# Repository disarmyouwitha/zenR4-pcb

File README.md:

# Steno Squid QSPI expansion module

Current hardware work is the [Steno Squid eight-contact daughterboard](projects/steno-squid/README.md) for the Boardsource Wireless Corne SMT. Its first electrical proposal is available in native KiCad. Connector dimensions, supply verification and exact flash package are the next design inputs.

## Completed Draft-Corne routing reference

# Draft-Corne: Choc Corne with left flash / right nice!view

**[Draft C files and status](projects/choc-corne-flash/draft-c/README.md)** · [ChatGPT handoff](docs/CHATGPT-HANDOFF.md) · [Download packet](docs/draft-corne.zip)

Both nice!nanos mount on the front, components down. Our tested matrix and left QSPI are retained; the right has a real nice!view interface. Battery connections use back-side solder pads. Both halves are routed and pass KiCad ERC, DRC, and schematic parity checks. Physical assembly still needs verification.

Repository remains private; preserve [source attribution](ATTRIBUTION.md). The older Draft B information below is historical.

---

# zenR4-pcb — Nano Independent

Historical Draft B direction: our own 42-key Choc nice!nano keyboard and case, inspired by Zen geometry. The owner is pursuing an original spare PCB for their Zen; integrated replacement development is set aside.

## Historical draft: B

- Old rear USB reliefs removed; USB-C comes from the nice!nano.
- Thumb clearance bubble replaced by a smooth, mirrored contour.
- All electrical objects and switch centers preserved from Draft A.
- Both halves pass native ERC, DRC, unconnected and schematic parity checks with zero issues.

**[Open Draft B](projects/nano-independent/draft-b/README.md)** · [Thumb before/after](projects/nano-independent/draft-b/thumb-before-after.png) · [Current ChatGPT handoff](docs/CHATGPT-HANDOFF.md) · [Download Draft B packet](docs/nano-independent-draft-b.zip)

Right nice!view, optional flash population, optional RGB and squid art remain the target. Their new display/RGB circuits and the new case are not implemented by this outline-only revision. See [project direction](projects/nano-independent/README.md).

Open the `zen-r4-left.kicad_pro` / `zen-r4-right.kicad_pro` under `projects/nano-independent/draft-b/`. `r4-layout/` is the unchanged Draft A baseline, also tagged `draft-a-baseline`; its old case-fit notes and upload ZIP are historical. Experimental generators can overwrite finished work.

For tomorrow's ChatGPT discussion, use [START-HERE](docs/START-HERE.md). Private GitHub links may require your signed-in account; upload the handoff/images if ChatGPT cannot read the repo.

Repository visibility remains private. Restricted source CAD and derived files retain their attribution and source restrictions; see [ATTRIBUTION](ATTRIBUTION.md). No hardware/fabrication order or production readiness is claimed.

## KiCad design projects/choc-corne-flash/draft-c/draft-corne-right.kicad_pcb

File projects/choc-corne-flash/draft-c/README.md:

# Draft-Corne (Draft C)

42-key Typeractive-style Choc-spaced Corne with our tested matrix, left QSPI flash and right nice!view. This is a routed development draft, not a manufacturing release. The geometry was reconstructed from a public 3D model; it is not Typeractive's original PCB source. See the reference folder and root ATTRIBUTION.md.

Open `draft-corne-left.kicad_pro` or `draft-corne-right.kicad_pro` beside their matching schematic and PCB. Keep the local symbol library, footprint directory and library tables with the files.

## Assembly direction

- Both nice!nanos mount on the **front**, with **components facing down** toward the carrier PCB, as explicitly requested. Both have the same physical pin-bank orientation: top view, USB up, carrier U1 pad 1 is on the right and pad 13 on the left.
- Choc sockets and diodes are on the back. The left top-row innermost socket SW6 is rotated 180 degrees and D6 moved to avoid mounting-hole/socket clearances; its switch center and electrical assignment are unchanged.
- Left flash U2 and local 100 nF C1 / 10 kΩ R1 occupy the former JST electronics region, on the front. Candidate flash is W25Q128JVSIQ, **208-mil SOIC**, not the narrower SOIC package.
- Battery J1 is a pair of **back-side solder pads**: 1 BAT+, 2 GND. No JST. Plan strain relief and insulated battery retention in the new enclosure. Reset is on the opposite face in this area.
- Right J2 supplies a nice!view above the nano. Routing moved J2 1.8 mm toward the thumbs to clear the carrier’s antenna keepout. Check display height and solder access with the actual parts.
- Power/reset footprints are candidates (MSK12C02 / TL3342), pending exact purchased-part drawing checks. The battery switch disconnects the cell; USB can still power the nano. Charging while switched off is not promised.

## Pin plan

Both halves retain ROW0–3 = D8, D9, D21, D20; COL0–5 outside→seam = D19, D18, D15, D14, D0, D1. Col2row diodes; right firmware reverses column scan with global offset 6. This is **our matrix**, not stock Typeractive D4–D7 rows.

Left flash CS#/CLK/IO0/IO1/IO2/IO3 = D2/D4/D5/D6/D7/D3, plus switched 3V3 and GND. The nano controls the switched rail internally using P0.13; that GPIO is not a carrier edge pad.

Right nice!view J2, viewed from the front, left→right:

| Pad | Signal | nice!nano |
|---|---|---|
| 1 | MOSI | D2 / P0.17 |
| 2 | SCK | D3 / P0.20 |
| 3 | VCC | switched 3V3 |
| 4 | GND | GND |
| 5 | CS, active high | D4 / P0.22 |

The custom right CS is D4; the existing Ultralight's D0 CS cannot be copied because D0 is one of our matrix columns. Working hardware/firmware has not been altered.

## Checks and remaining work

Both halves have **zero unrouted connections, DRC violations, schematic parity issues, and ERC violations** in KiCad 10.0.7. Both copper layers have filled ground planes. The carrier’s antenna keepout remains clear. See `validation.json` for hashes and configured checks. The DSN/SES files and placement/router reports are records of the initial routing pass.

Physical assembly remains unverified. Check the nano and display stack, the selected footprints against the parts, and battery retention before fabrication.

Official display references are the [pinout](https://nicekeyboards.com/docs/nice-view/pinout-schematic/) and [dimensions](https://nicekeyboards.com/static/2f2592ff1ff8021932814b20cb76e3c4/a6d36/niceview_dimensions.png).

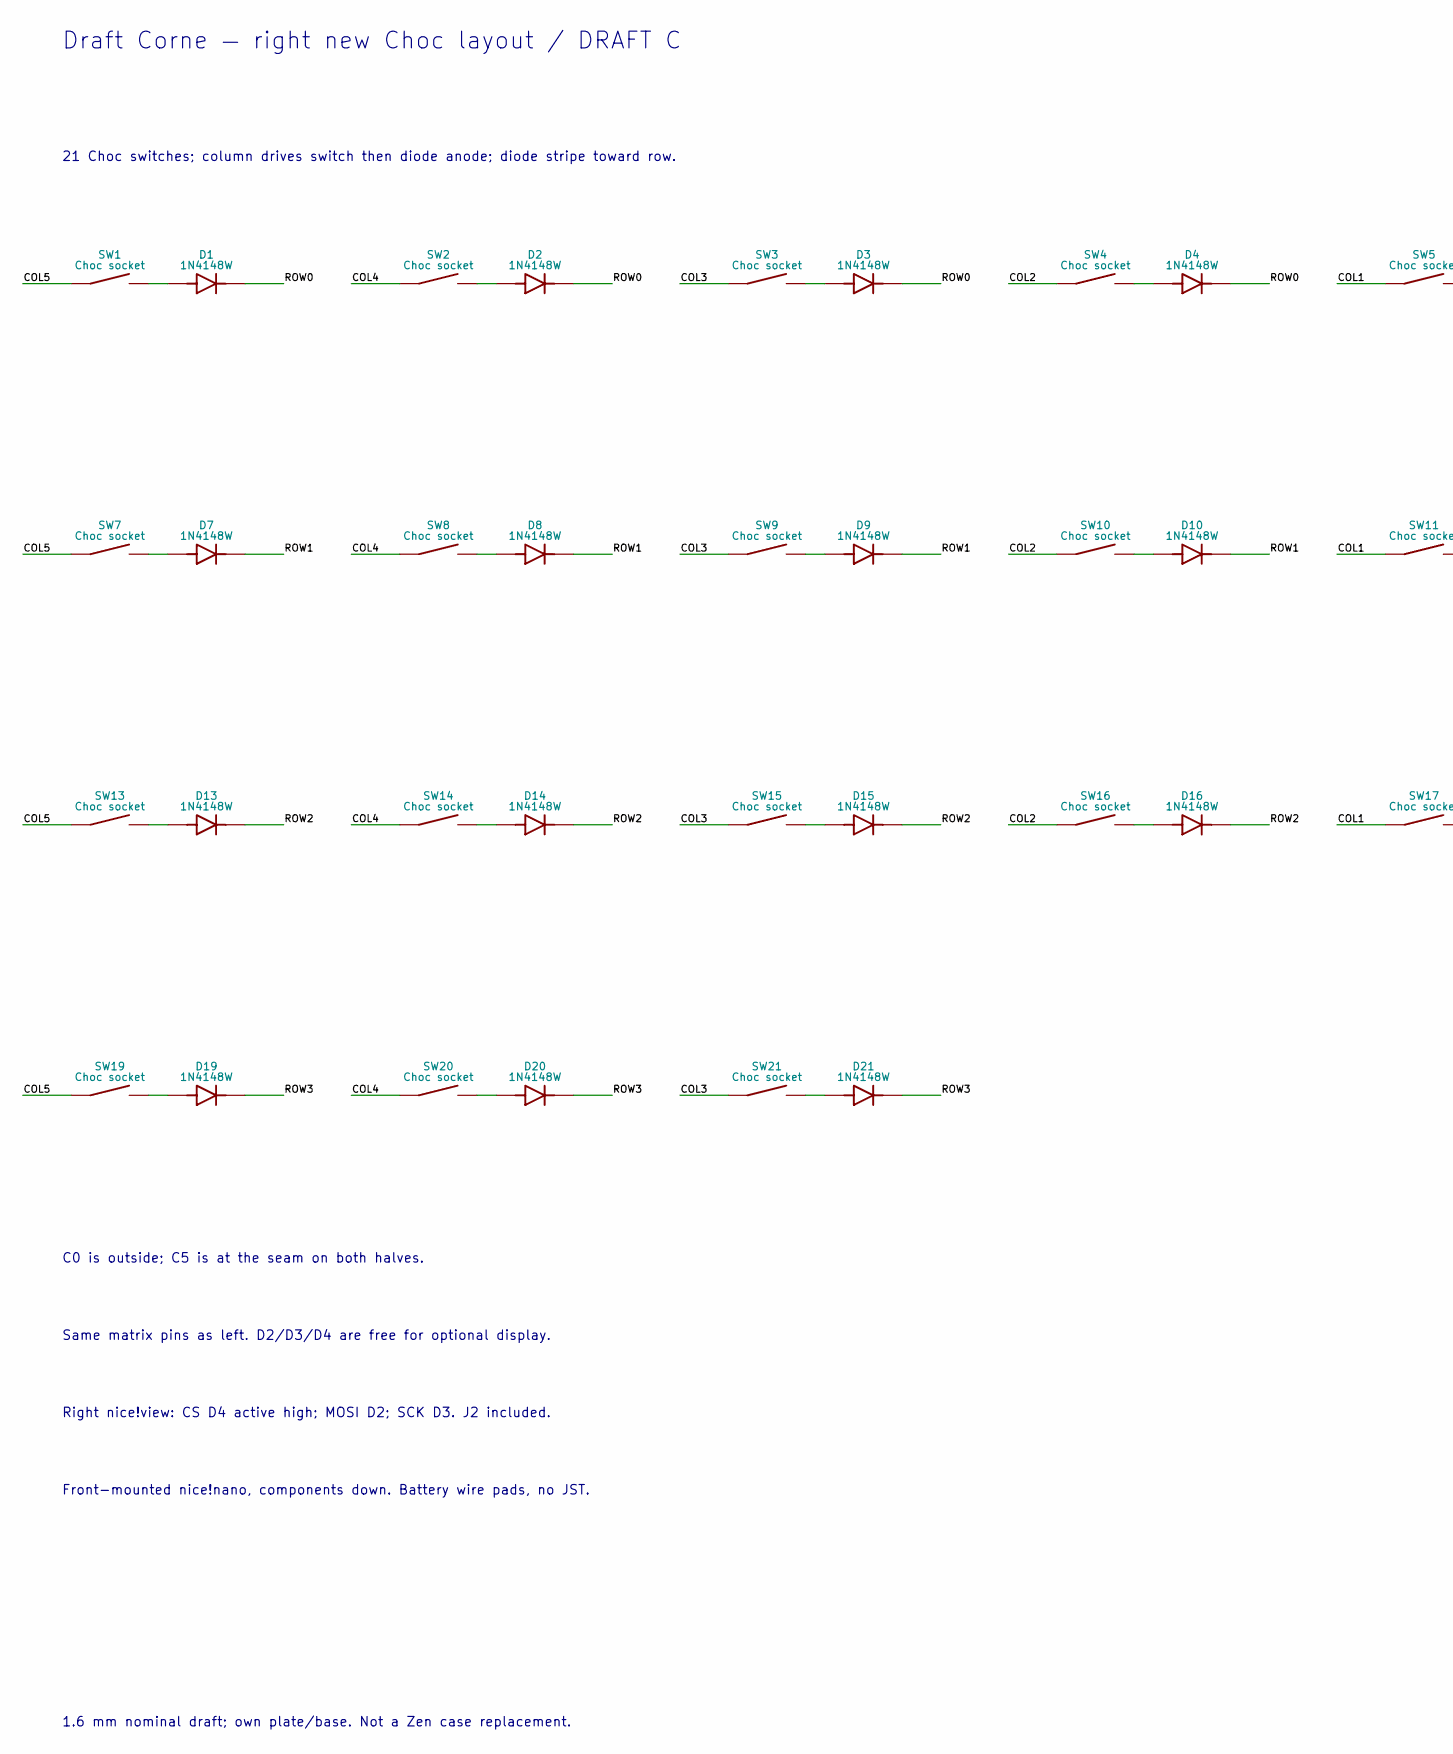
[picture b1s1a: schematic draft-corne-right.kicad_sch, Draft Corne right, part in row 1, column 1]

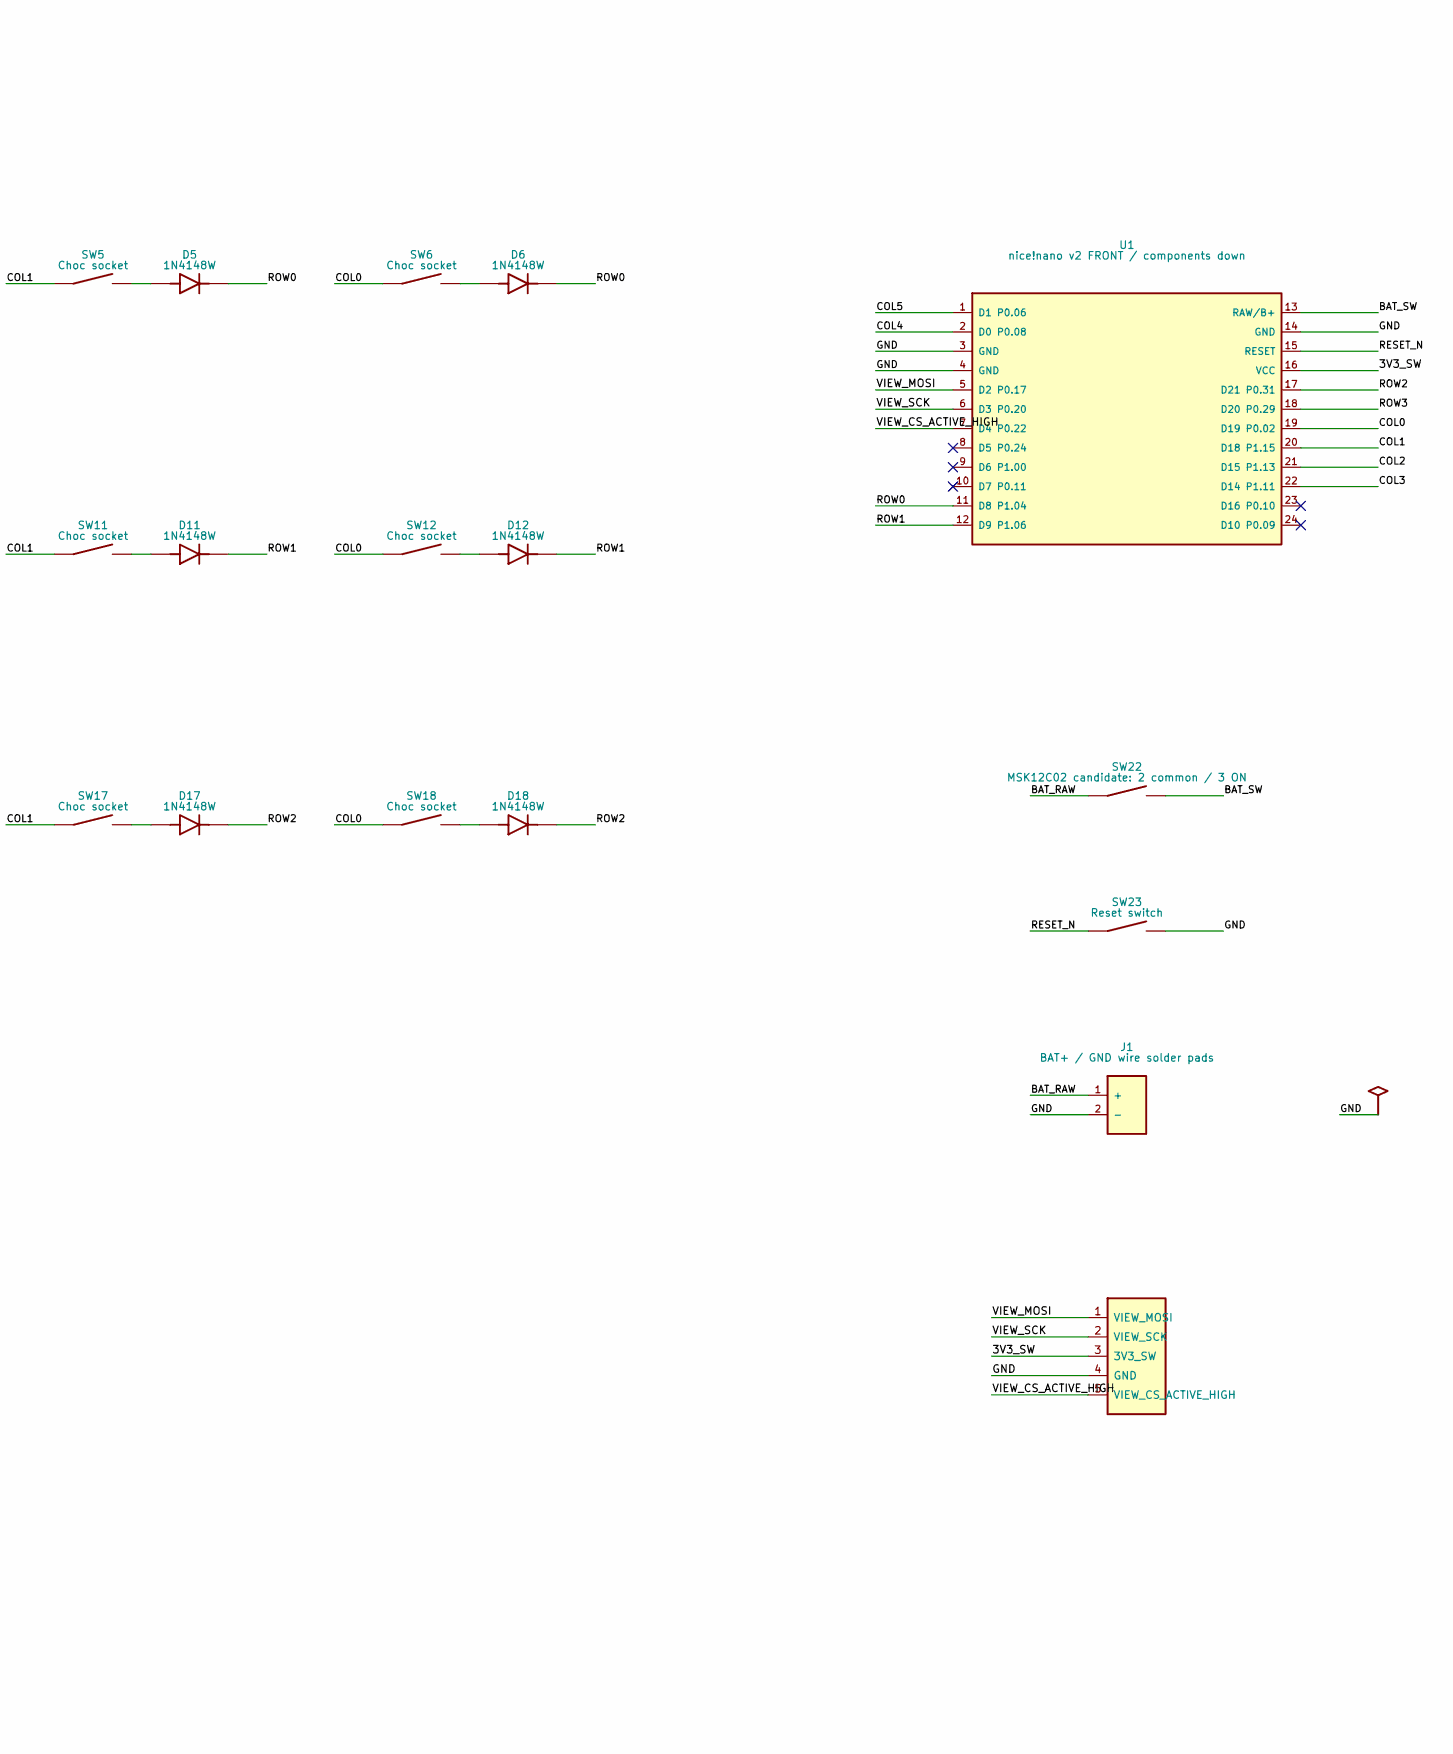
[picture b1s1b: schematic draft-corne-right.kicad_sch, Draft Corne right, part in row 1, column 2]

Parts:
D1, D2, D3, D4, D5, D6, D7, D8, D9, D10, D11, D12, D13, D14, D15, D16, D17, D18, D19, D20, D21: 1N4148W; Diode_SOD123_Bottom
J1: BAT+ / GND wire solder pads; Battery_Wire_SMD
J2: nice!view front header; NiceView_Front_Header
SW1, SW2, SW3, SW4, SW5, SW6, SW7, SW8, SW9, SW10, SW11, SW12, SW13, SW14, SW15, SW16, SW17, SW18, SW19, SW20, SW21: Choc socket; ChocSocket_Bottom
SW22: MSK12C02 candidate: 2 common / 3 ON; Power_MSK12C02
SW23: Reset switch; Reset_TL3342
U1: nice!nano v2 FRONT / components down; Nano_Front_Down

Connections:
/3V3_SW: J2.3 (3V3_SW), U1.16 (VCC)
/BAT_RAW: J1.1 (+), SW22.2 (1)
/BAT_SW: SW22.3 (2), U1.13 (RAW/B+)
/COL0: SW6.1, SW12.1, SW18.1, U1.19 (D19 P0.02)
/COL1: SW5.1, SW11.1, SW17.1, U1.20 (D18 P1.15)
/COL2: SW4.1, SW10.1, SW16.1, U1.21 (D15 P1.13)
/COL3: SW3.1, SW9.1, SW15.1, SW21.1, U1.22 (D14 P1.11)
/COL4: SW2.1, SW8.1, SW14.1, SW20.1, U1.2 (D0 P0.08)
/COL5: SW1.1, SW7.1, SW13.1, SW19.1, U1.1 (D1 P0.06)
/GND: J1.2 (-), J2.4 (GND), SW23.2, U1.3 (GND), U1.4 (GND), U1.14 (GND)
/RESET_N: SW23.1, U1.15 (RESET)
/ROW0: D1.1 (K), D2.1 (K), D3.1 (K), D4.1 (K), D5.1 (K), D6.1 (K), U1.11 (D8 P1.04)
/ROW1: D7.1 (K), D8.1 (K), D9.1 (K), D10.1 (K), D11.1 (K), D12.1 (K), U1.12 (D9 P1.06)
/ROW2: D13.1 (K), D14.1 (K), D15.1 (K), D16.1 (K), D17.1 (K), D18.1 (K), U1.17 (D21 P0.31)
/ROW3: D19.1 (K), D20.1 (K), D21.1 (K), U1.18 (D20 P0.29)
/VIEW_CS_ACTIVE_HIGH: J2.5 (VIEW_CS_ACTIVE_HIGH), U1.7 (D4 P0.22)
/VIEW_MOSI: J2.1 (VIEW_MOSI), U1.5 (D2 P0.17)
/VIEW_SCK: J2.2 (VIEW_SCK), U1.6 (D3 P0.20)
unnamed: D1.2 (A), SW1.2
unnamed: D2.2 (A), SW2.2
unnamed: D3.2 (A), SW3.2
unnamed: D4.2 (A), SW4.2
unnamed: D5.2 (A), SW5.2
unnamed: D6.2 (A), SW6.2
unnamed: D7.2 (A), SW7.2
unnamed: D8.2 (A), SW8.2
unnamed: D9.2 (A), SW9.2
unnamed: D10.2 (A), SW10.2
unnamed: D11.2 (A), SW11.2
unnamed: D12.2 (A), SW12.2
unnamed: D13.2 (A), SW13.2
unnamed: D14.2 (A), SW14.2
unnamed: D15.2 (A), SW15.2
unnamed: D16.2 (A), SW16.2
unnamed: D17.2 (A), SW17.2
unnamed: D18.2 (A), SW18.2
unnamed: D19.2 (A), SW19.2
unnamed: D20.2 (A), SW20.2
unnamed: D21.2 (A), SW21.2

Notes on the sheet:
Draft Corne — right new Choc layout / DRAFT C
21 Choc switches; column drives switch then diode anode; diode stripe toward row.
C0 is outside; C5 is at the seam on both halves.
Same matrix pins as left. D2/D3/D4 are free for optional display.
Right nice!view: CS D4 active high; MOSI D2; SCK D3. J2 included.
Front-mounted nice!nano, components down. Battery wire pads, no JST.
1.6 mm nominal draft; own plate/base. Not a Zen case replacement.

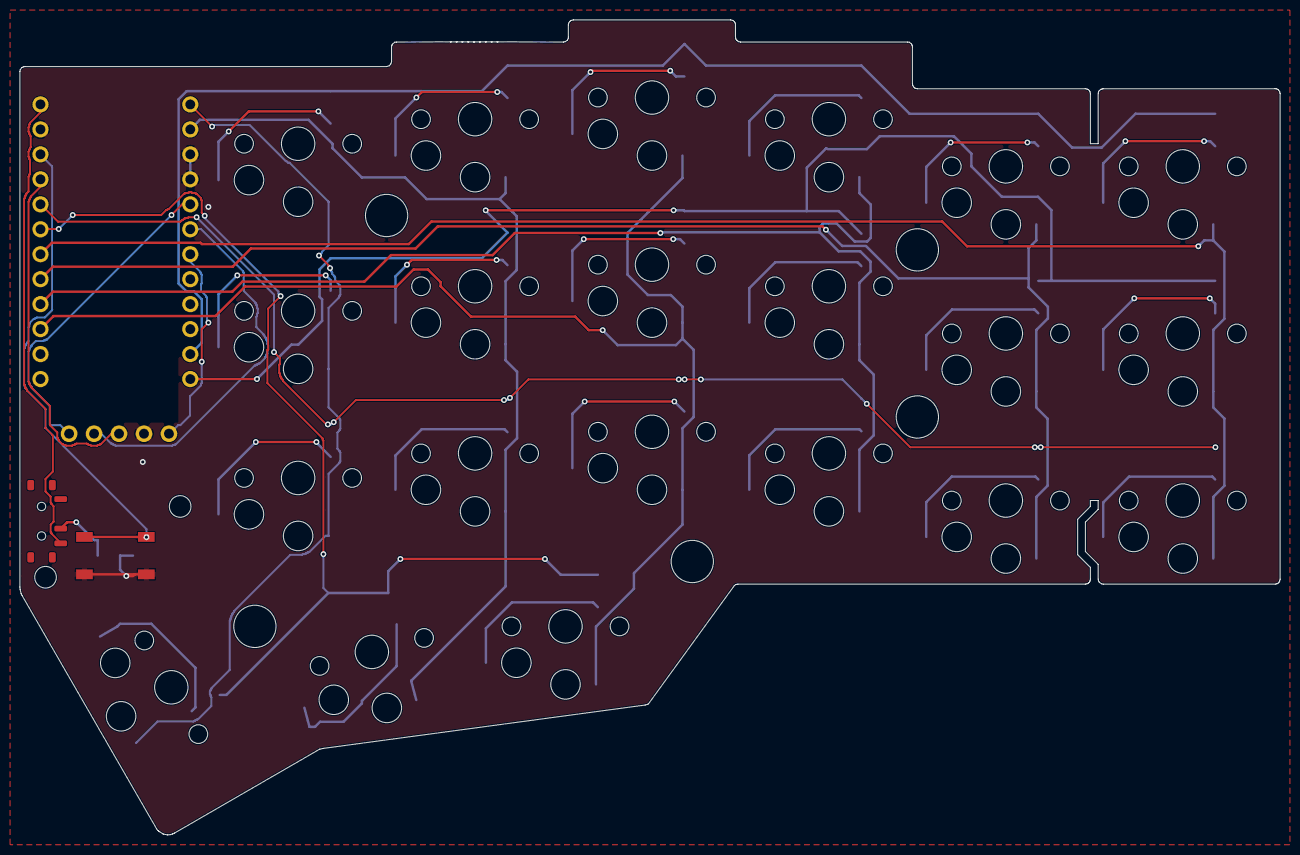
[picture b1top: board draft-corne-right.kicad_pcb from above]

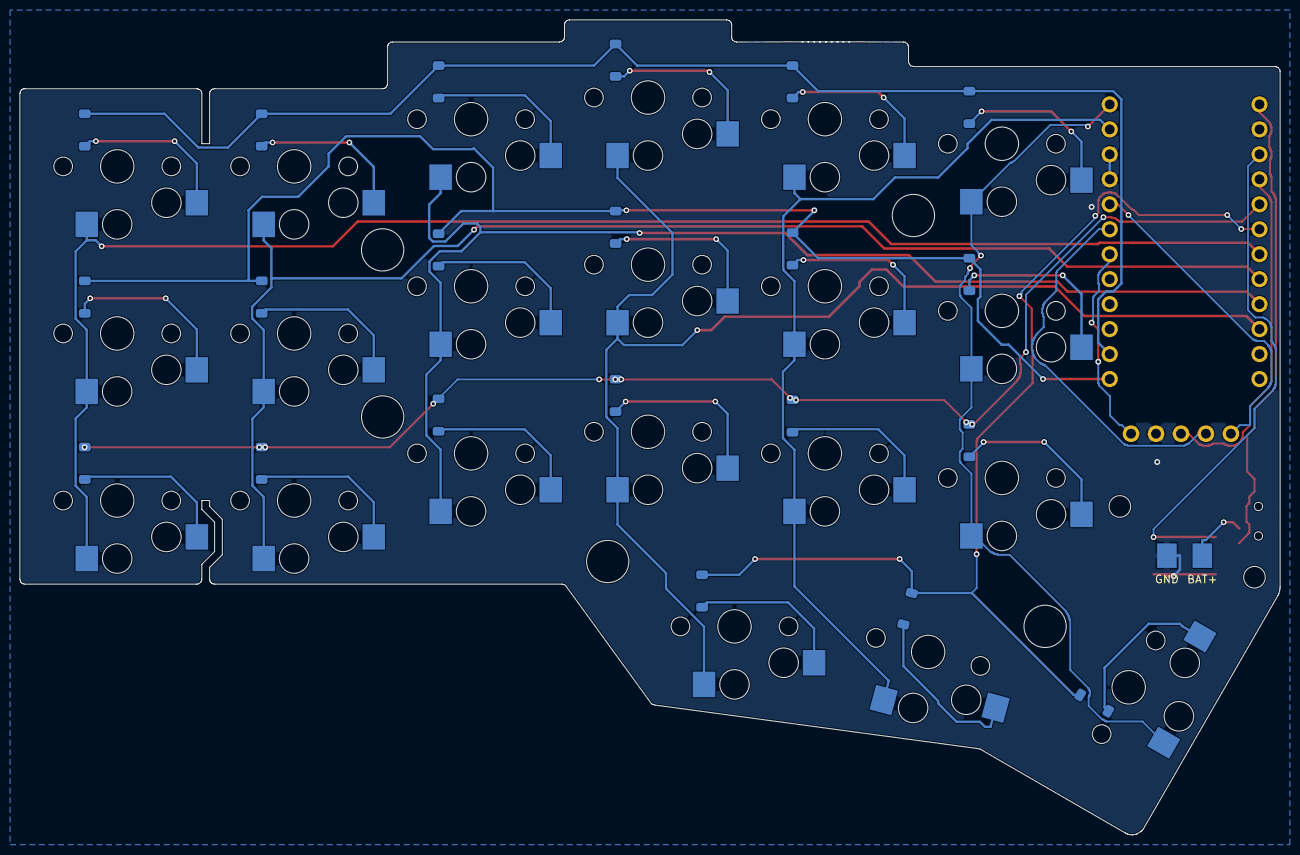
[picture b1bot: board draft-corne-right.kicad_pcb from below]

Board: 2 copper layers, 128.2 x 82.9 mm, 54 parts (43 on the bottom side), 39 nets.

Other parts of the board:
H1, H2, H3, H4, H6: Mount_4p3
H5, H7: Mount_2p2

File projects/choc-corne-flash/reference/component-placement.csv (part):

side,reference,value,x_mm,y_mm,angle_deg,layer,description
left,SW1,Choc_hotswap_model,34.89901373177646,39.930963178102395,0.012644249271033713,B,Holes measured from GLB. SMD socket pads inferred from standard Choc socket geometry; verify pad numbering and land pattern.
left,D1,D_SOD123_INFERRED,38.19987499999999,36.13314,-90.0,B,Body and cathode stripe placement recovered. SOD-123 land pattern and col2row electrical connections inferred; diode part number unknown.
left,SW2,Choc_hotswap_model,52.89922665409529,39.93025331834761,0.006759346013110497,B,Holes measured from GLB. SMD socket pads inferred from standard Choc socket geometry; verify pad numbering and land pattern.
left,D2,D_SOD123_INFERRED,56.20455999999999,36.13314,-90.0,B,Body and cathode stripe placement recovered. SOD-123 land pattern and col2row electrical connections inferred; diode part number unknown.
left,SW3,Choc_hotswap_model,70.9008088288196,35.1313637185097,0.02038078131758709,B,Holes measured from GLB. SMD socket pads inferred from standard Choc socket geometry; verify pad numbering and land pattern.
left,D3,D_SOD123_INFERRED,74.201145,31.13364,-90.0,B,Body and cathode stripe placement recovered. SOD-123 land pattern and col2row electrical connections inferred; diode part number unknown.
left,SW4,Choc_hotswap_model,88.89973051288356,32.93110816247218,-0.03257012778338401,B,Holes measured from GLB. SMD socket pads inferred from standard Choc socket geometry; verify pad numbering and land pattern.
left,D4,D_SOD123_INFERRED,92.19772999999999,28.832409999999996,-90.0,B,Body and cathode stripe placement recovered. SOD-123 land pattern and col2row electrical connections inferred; diode part number unknown.
left,SW5,Choc_hotswap_model,106.89620271838191,35.133439650507626,0.022546590305529638,B,Holes measured from GLB. SMD socket pads inferred from standard Choc socket geometry; verify pad numbering and land pattern.
left,D5,D_SOD123_INFERRED,110.20241999999999,31.13364,-89.99971020439162,B,Body and cathode stripe placement recovered. SOD-123 land pattern and col2row electrical connections inferred; diode part number unknown.
left,SW6,Choc_hotswap_model,124.90000259765134,37.63267145241049,0.030524102335461892,B,Holes measured from GLB. SMD socket pads inferred from standard Choc socket geometry; verify pad numbering and land pattern.
left,D6,D_SOD123_INFERRED,128.19899999999998,33.65365,-90.0,B,Body and cathode stripe placement recovered. SOD-123 land pattern and col2row electrical connections inferred; diode part number unknown.
left,SW7,Choc_hotswap_model,34.89915641256381,56.930962876769456,0.012539873019652493,B,Holes measured from GLB. SMD socket pads inferred from standard Choc socket geometry; verify pad numbering and land pattern.
left,D7,D_SOD123_INFERRED,38.19987499999999,53.20599,-90.0,B,Body and cathode stripe placement recovered. SOD-123 land pattern and col2row electrical connections inferred; diode part number unknown.
left,SW8,Choc_hotswap_model,52.89936145200127,56.93101786715822,0.015041042203948576,B,Holes measured from GLB. SMD socket pads inferred from standard Choc socket geometry; verify pad numbering and land pattern.
left,D8,D_SOD123_INFERRED,56.20455999999999,53.20599,-90.0,B,Body and cathode stripe placement recovered. SOD-123 land pattern and col2row electrical connections inferred; diode part number unknown.
left,SW9,Choc_hotswap_model,70.89993719117419,52.13154086977602,0.032401923395911365,B,Holes measured from GLB. SMD socket pads inferred from standard Choc socket geometry; verify pad numbering and land pattern.
left,D9,D_SOD123_INFERRED,74.201145,48.352345,-90.0,B,Body and cathode stripe placement recovered. SOD-123 land pattern and col2row electrical connections inferred; diode part number unknown.
left,SW10,Choc_hotswap_model,88.8996719448901,49.931726544460005,0.02954781604569936,B,Holes measured from GLB. SMD socket pads inferred from standard Choc socket geometry; verify pad numbering and land pattern.
left,D10,D_SOD123_INFERRED,92.19772999999999,46.22938,-90.0,B,Body and cathode stripe placement recovered. SOD-123 land pattern and col2row electrical connections inferred; diode part number unknown.
left,SW11,Choc_hotswap_model,106.89798424378102,52.131845452681155,0.0342155624306564,B,Holes measured from GLB. SMD socket pads inferred from standard Choc socket geometry; verify pad numbering and land pattern.
left,D11,D_SOD123_INFERRED,110.20241999999999,48.303725,-89.99970780876369,B,Body and cathode stripe placement recovered. SOD-123 land pattern and col2row electrical connections inferred; diode part number unknown.
left,SW12,Choc_hotswap_model,124.9011587244321,54.63122607082637,0.012916640887988802,B,Holes measured from GLB. SMD socket pads inferred from standard Choc socket geometry; verify pad numbering and land pattern.
left,D12,D_SOD123_INFERRED,128.19899999999998,50.62926,-90.0,B,Body and cathode stripe placement recovered. SOD-123 land pattern and col2row electrical connections inferred; diode part number unknown.
left,SW13,Choc_hotswap_model,34.89916751621723,73.93096463681468,0.0013114946986480002,B,Holes measured from GLB. SMD socket pads inferred from standard Choc socket geometry; verify pad numbering and land pattern.
left,D13,D_SOD123_INFERRED,38.19987499999999,70.23022499999999,-90.0,B,Body and cathode stripe placement recovered. SOD-123 land pattern and col2row electrical connections inferred; diode part number unknown.
left,SW14,Choc_hotswap_model,52.89931490531896,73.9309029911515,-0.003375768003982743,B,Holes measured from GLB. SMD socket pads inferred from standard Choc socket geometry; verify pad numbering and land pattern.
left,D14,D_SOD123_INFERRED,56.20455999999999,70.23022499999999,-90.0,B,Body and cathode stripe placement recovered. SOD-123 land pattern and col2row electrical connections inferred; diode part number unknown.
left,SW15,Choc_hotswap_model,70.90086378173342,69.13134612814801,0.015995142904135895,B,Holes measured from GLB. SMD socket pads inferred from standard Choc socket geometry; verify pad numbering and land pattern.
left,D15,D_SOD123_INFERRED,74.201145,65.433295,-90.0,B,Body and cathode stripe placement recovered. SOD-123 land pattern and col2row electrical connections inferred; diode part number unknown.
left,SW16,Choc_hotswap_model,88.90044136728201,66.93031822857623,0.0033833274749352302,B,Holes measured from GLB. SMD socket pads inferred from standard Choc socket geometry; verify pad numbering and land pattern.
left,D16,D_SOD123_INFERRED,92.19772999999999,63.13207,-90.0,B,Body and cathode stripe placement recovered. SOD-123 land pattern and col2row electrical connections inferred; diode part number unknown.
left,SW17,Choc_hotswap_model,106.89933079746973,69.13033538743824,0.008502805034760868,B,Holes measured from GLB. SMD socket pads inferred from standard Choc socket geometry; verify pad numbering and land pattern.
left,D17,D_SOD123_INFERRED,110.20241999999999,65.32795999999999,-89.99971020439162,B,Body and cathode stripe placement recovered. SOD-123 land pattern and col2row electrical connections inferred; diode part number unknown.
left,SW18,Choc_hotswap_model,124.90052043677505,71.63222556971846,0.03424305665980184,B,Holes measured from GLB. SMD socket pads inferred from standard Choc socket geometry; verify pad numbering and land pattern.
left,D18,D_SOD123_INFERRED,128.19899999999998,67.83176,-90.0,B,Body and cathode stripe placement recovered. SOD-123 land pattern and col2row electrical connections inferred; diode part number unknown.
left,SW19,Choc_hotswap_model,97.6995885927662,86.73153858729248,0.02868599105267802,B,Holes measured from GLB. SMD socket pads inferred from standard Choc socket geometry; verify pad numbering and land pattern.
left,D19,D_SOD123_INFERRED,100.99749999999999,83.130075,-90.0,B,Body and cathode stripe placement recovered. SOD-123 land pattern and col2row electrical connections inferred; diode part number unknown.
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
